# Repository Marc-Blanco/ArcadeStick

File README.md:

# ArcadeStick
---
This is an actual arcadestick with the purpose of being a controller, specifically designed for Fighting Games, but specifically Tekken or other 3D fighters because of the use of a Korean lever _Korean levers have a stronger rubber which is perfect for returning quickly to neutral inputs but is slightly harder to make qcf-esque inputs_. I also wanted to add a little bit of personalization, and flavour it, so I'll try and add more variants of Cases. The project uses the SAMDUCKSA CWL-NEWHELPME lever and SANWA OBSF-24 buttons but other components could work (mainly Korean levers, japanese or inclusive the rare american sticks could not work because of the shaft space, if you want to try the popular neoknee lever, ~99$, it probably will work). I wanted to make this project because I wanted to try make a controller myself because the other options are very expensive and eventhough for unexperienced people on the community this might seem expensive it the complete opposite.
The Controller consists of a lever, 8 buttons which are all soldered into SMD connectors. An Oled lcd screen and 3 other push buttons as additonal buttons.

## CASE

## PCB

## Schematic

## Firmware
I haven't worked on it yet but this rep will carry me. https://github.com/OpenStickCommunity/GP2040-CE?tab=readme-ov-file

## BOM
| Part                                 | Quantity | Price  | Link                                                                                                                                                                                                                                                                                                                                                                                                                                                                                          | Notes                                                      |
| ------------------------------------ | -------- | ------ | --------------------------------------------------------------------------------------------------------------------------------------------------------------------------------------------------------------------------------------------------------------------------------------------------------------------------------------------------------------------------------------------------------------------------------------------------------------------------------------------- | ---------------------------------------------------------- |
| PCB                          | 5        | $9.40 | [JLCPCB](https://jlcpcb.com/) | Any other pcb company will do         |
| Buttons - SANWA OBSF 24 | 8        | 2.50 € | [Smallcab](https://www.smallcab.net/sanwa-obsf-24mm-pushbutton-black-p-782.html?osCsid=f7bb76566ca868ea6122a69b92dd5b78) | French Vendor which is good if you are from the EU but there's a lot of US companies that sell various parts (they normally don't ship outside US)  
| Lever- CWL-NEWHELPME | 1      | 67,66€  |[Smallcab](https://www.smallcab.net/helpme-c-30_91_80_345.html) | Same as above. Sadly this is a normal price range for joysticks, I don't know any more budget friendly alternatives but if you want expensive there's always the Golden Fanta or Neo Knee lever        
| Raspberrypi Pico                 | 1       | $0.99  | [Aliexpress](https://es.aliexpress.com/item/1005003371056277.html?spm=a2g0o.productlist.main.1.64b0TBujTBujqQ&algo_pvid=f291c49f-37b8-4414-9bc8-1c92e40f57c4&pdp_ext_f=%7B%22order%22%3A%222296%22%2C%22eval%22%3A%221%22%7D&utparam-url=scene%3Asearch%7Cquery_from%3A) | Aliexpress Quality     
 | Total cost | | 113.35$ | | Sorry Hackclub 😞, I tried to make it cheaper but couldn't.                                                                                                                                                                                                                                              
### Zine

---
### Thanks to:

SANWA-DENSHI[:](https://www.sanwa-d.co.jp/product/web)

SAMDUCKSA[:](http://samducksa.com/new/product/index_view.php?UidNum=407)

SLAGCOIN[:](https://www.slagcoin.com/joystick/layout/shift36_l.png) _they also have other designs that you could use_

-for helping the design

[This reddit post for the inspiration](https://www.reddit.com/r/fightsticks/comments/1kiasqy/miku_mojubox_mikubox_early_fsf_submission/?solution=ff437812c4b2a38bff437812c4b2a38b&js_challenge=1&token=bbbe4bf1c9a2b5160829c4be34da58612d497acc7a3828f39123863a3690014b)

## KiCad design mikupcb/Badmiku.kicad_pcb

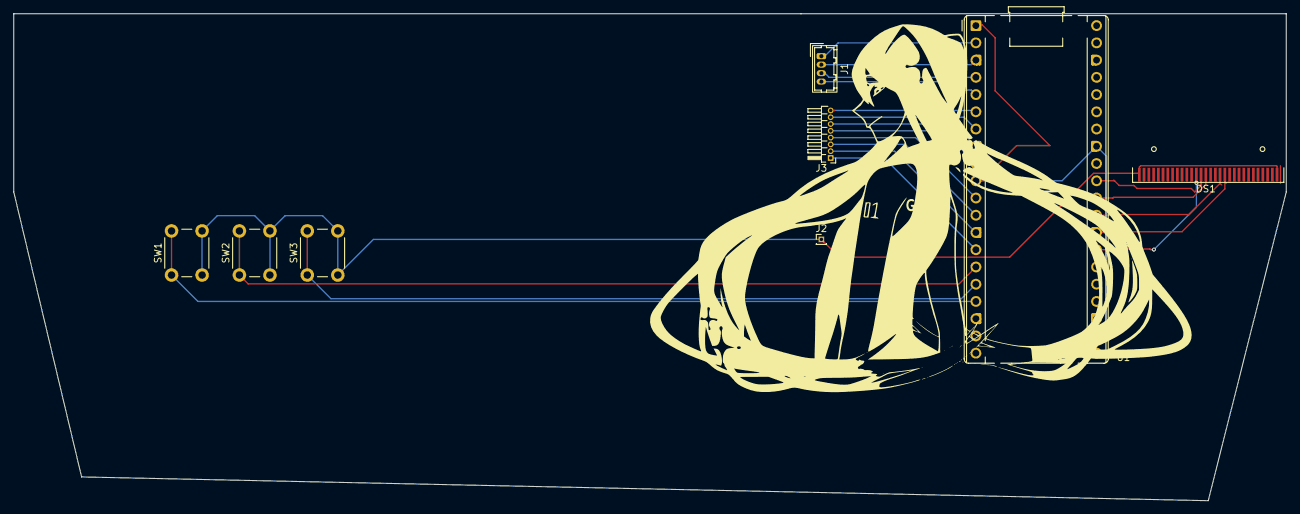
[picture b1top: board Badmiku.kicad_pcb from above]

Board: 2 copper layers, 187.5 x 71.8 mm, 8 parts (0 on the bottom side), 22 nets.

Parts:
DS1: OLED-128O064D
J1: Conn_01x04_Pin; Hirose_DF13-04P-1.25DSA_1x04_P1.25mm_Vertical
J2: Conn_01x01_Pin; PinHeader_1x01_P1.00mm_Vertical
J3: Conn_01x08_Pin; PinHeader_1x08_P1.00mm_Horizontal
SW1, SW2, SW3: SW_Push; SW_PUSH_6mm
U1: RP2040; RaspberryPi_Pico_Common_THT

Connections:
/A: DS1.15 (D/~C), U1.30 (GPIO19)
/Coin?: SW1.1, U1.17 (GPIO14)
/E: DS1.19 (D1), U1.28 (GPIO17)
/GND: DS1.1 (GND), DS1.30 (GND), J2.1 (Pin_1_1), SW1.2, SW2.2, SW3.2
/Select: SW3.1, U1.16 (GPIO13)
/Start: SW2.1, U1.15 (GPIO12)
/V: DS1.18 (D0), U1.29 (GPIO18)
/W: DS1.13 (~CS), U1.27 (GPIO16)
/X: DS1.14 (~RES), U1.31 (GPIO20)
unnamed: J1.1, U1.2 (GPIO0)
unnamed: J1.2, U1.3 (GPIO1)
unnamed: J1.3, U1.4 (GPIO2)
unnamed: J1.4, U1.5 (GPIO3)
unnamed: J3.1, U1.14 (GPIO11)
unnamed: J3.2, U1.13 (GPIO10)
unnamed: J3.3, U1.12 (GPIO9)
unnamed: J3.4, U1.11 (GPIO8)
unnamed: J3.5, U1.9 (GPIO7)
unnamed: J3.6, U1.8 (GPIO6)
unnamed: J3.7, U1.7 (GPIO5)
unnamed: J3.8, U1.6 (GPIO4)
unnamed: U1.1 (IOVDD), U1.10 (IOVDD), U1.22 (IOVDD), U1.33 (IOVDD)

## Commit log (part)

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2026-04-10 Create a
2026-04-24 Rename CAD/Mikustick-Bottom.step to CAD/v1/Mikustick-Bottom.step
2026-04-24 Rename CAD/Mikustick-Button.step to CAD/v1/Mikustick-Button.step
2026-04-24 Rename CAD/Mikustick-Mid.step to CAD/v1/Arcadestick-Mid.step
2026-04-24 Rename miku.step to Arcadestick-top.step
2026-04-24 Rename Mikustick-Button.step to Arcadestick-Button.step
2026-04-24 Rename CAD/Arcadestick-top.step to CAD/v1/Arcadestick-top.step
2026-04-24 Rename CAD/Mikustick-Stick.step to CAD/v1/Arcadestick-Stick.step
2026-04-24 Rename Mikustick-Bottom.step to Arcadestick-Bottom.step
2026-04-24 Rename zinearcadestick.png to zine.png
2026-04-25 Update README with project motivation
    Added a personal motivation for the project to the README.
2026-06-03 Rename zine.png to images/zine.png
